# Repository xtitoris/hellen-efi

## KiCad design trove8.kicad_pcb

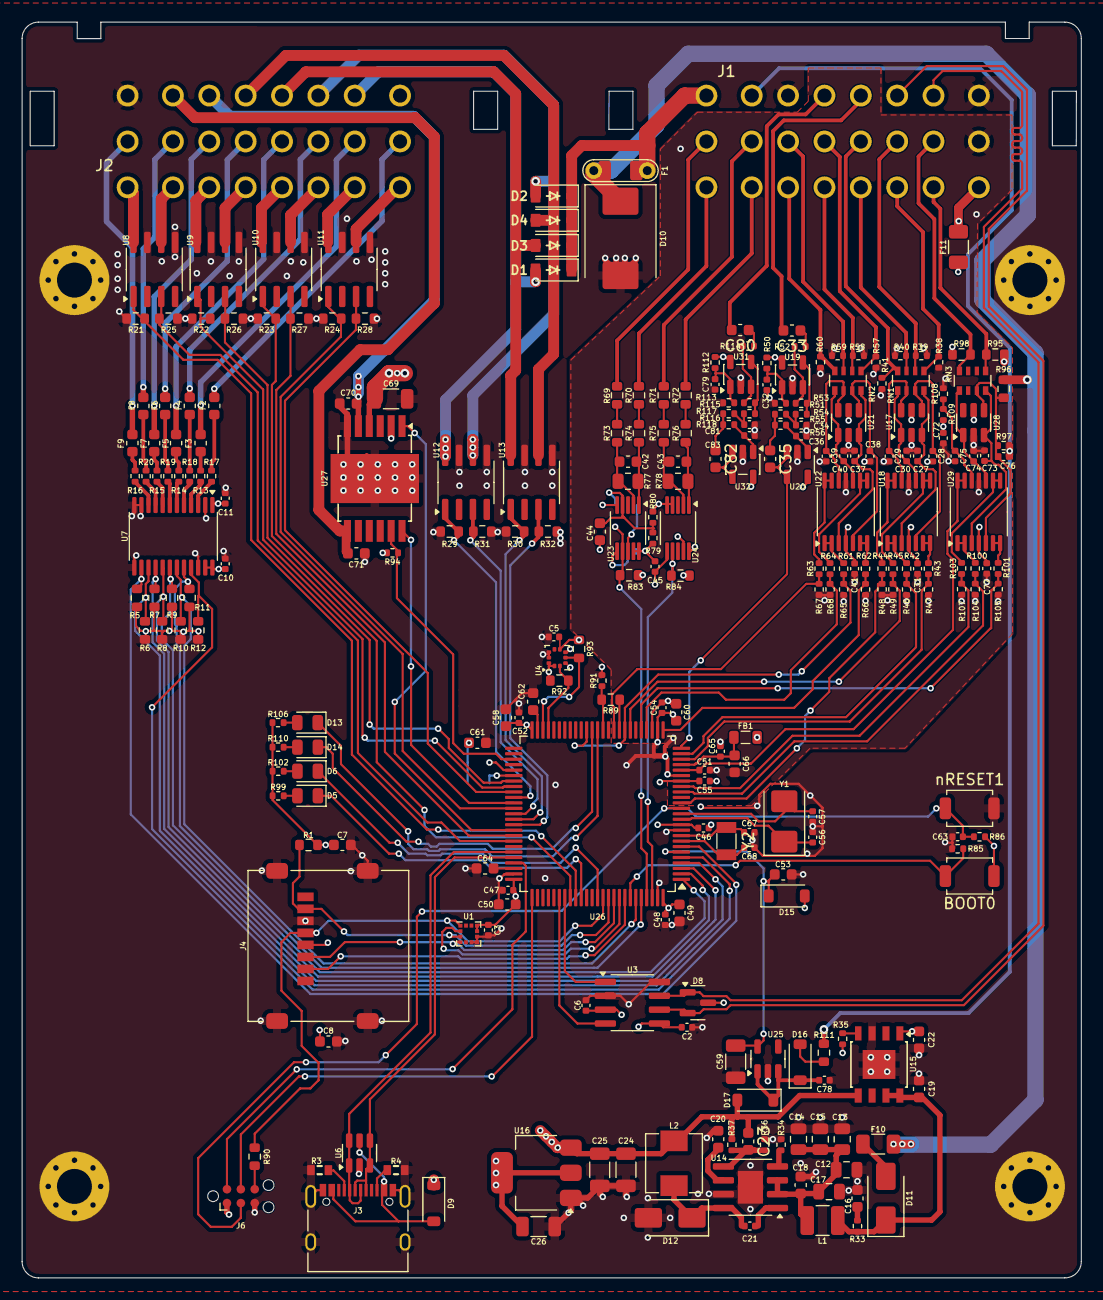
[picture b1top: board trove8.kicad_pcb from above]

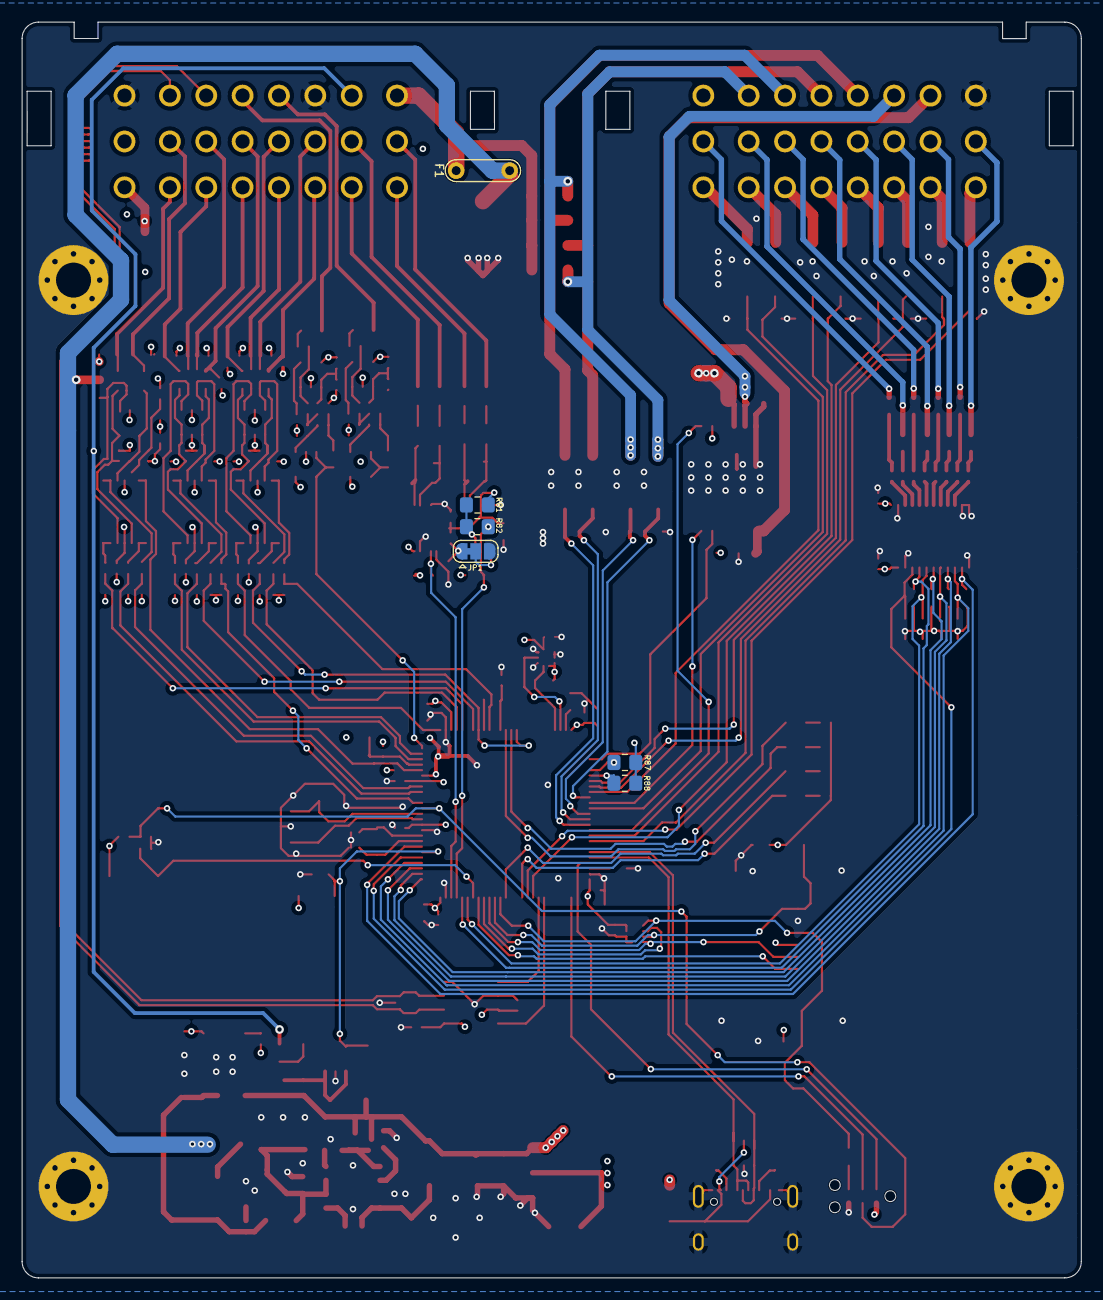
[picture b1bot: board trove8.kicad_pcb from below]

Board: 4 copper layers, 97.0 x 115.0 mm, 274 parts (5 on the bottom side), 204 nets.

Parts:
BOOT0: SW_Push; SW_SPST_TS-1088-xR020
C2, C3, C5, C6, C10, C11, C21, C27, C28, C29, C30, C31, C37, C38, C39, C40, C41, C45, C46, C47, C48, C51, C52, C54, C55, C63, C65, C72, C73, C74, C75, C77, C78: 100n; C_0402_1005Metric
C7, C8: 22u; C_0603_1608Metric
C12, C13, C14, C15, C17: 10u; C_0805_2012Metric
C16, C49, C50, C53, C58, C60, C66: 4.7u; C_0603_1608Metric
C18, C19, C22, C44, C61: 1u; C_0603_1608Metric
C20, C70, C71: 10n; C_0603_1608Metric
C23, C35, C82: 330p; C_0603_1608Metric
C24, C69: 10u; C_1206_3216Metric
C25, C26, C59: 47u; C_1206_3216Metric
C32, C79: 10n; C_0402_1005Metric
C33, C80: 3.3n; C_0603_1608Metric
C34, C81: 680p; C_0402_1005Metric
C36, C83: 47p; C_0402_1005Metric
C42, C43: 1n; C_0603_1608Metric
C56, C57: 18p; C_0402_1005Metric
C62, C64: 2.2u; C_0603_1608Metric
C67, C68: 15p; C_0402_1005Metric
C76: 1u; C_0402_1005Metric
D1, D2, D3, D4: B5819W; SOD-123
D5: RED; LED_0805_2012Metric
D6: GREEN; LED_0805_2012Metric
D8: PESD1CAN; SOT-23
D9, D15, D16, D17: 1N5819WS; D_SOD-123
D10: SM15T33CA; D_SMC
D11, D12: SS34; D_SMA
D13: BLUE; LED_0805_2012Metric
D14: YELLOW; LED_0805_2012Metric
F1: 12H1500D; PAD-1206-PAD
F2, F3, F4, F5, F6, F7, F8, F9: 50mA; Fuse_0603_1608Metric
F10: Polyfuse; Fuse_1206_3216Metric
F11: 120mA; Fuse_1206_3216Metric
FB1: Ferrite_Bead; L_0805_2012Metric
H1, H2, H3, H4: M3; MountingHole_3.2mm_M3_Pad_Via
J1: CONN_INPUTS; Delphi_Sicma_24_Black
J2: CONN_OUTPUTS; Delphi_Sicma_24_Grey
J3: USB_C
J4: Micro_SD_Card; microSD_HC_Molex_47219-2001
J6: Conn_01x06; Tag-Connect_TC2030-IDC-NL_2x03_P1.27mm_Vertical
JP1: Jumper_3_Bridged12; SolderJumper-3_P1.3mm_Bridged12_RoundedPad1.0x1.5mm
L1: 2.2u; L_1210_3225Metric
L2: 10u; MWSA0503
NT1: NetTie_2; NetTie-2_SMD_Pad0.5mm
R1: 33k; R_0603_1608Metric
R3, R4: 5.6k; R0603
R5, R6, R7, R8, R9, R10, R11, R12, R21, R22, R23, R24, R25, R26, R27, R28, R29, R30, R31, R32, R69, R70, R71, R72, R73, R74, R75, R76, R83, R84: 4.7k; R_0603_1608Metric
R13, R14, R15, R16, R17, R18, R19, R20: 10; R_0402_1005Metric
R33: 1; R_0402_1005Metric
R34, R35, R85, R86, R91, R94, R97: 10k; R_0402_1005Metric
R36, R54, R116: 12k; R_0402_1005Metric
R37: 68k; R_0402_1005Metric
R38, R39, R40, R41, R53, R57, R58, R59, R60, R115: 470k; R_0402_1005Metric
R42, R43, R44, R45, R46, R47, R48, R49, R61, R62, R63, R64, R65, R66, R67, R68, R100, R101, R103, R104, R105, R107, R108, R109: 4k7; R_0402_1005Metric
R50, R51, R56, R112, R113, R118: 33k; R_0402_1005Metric
R52, R55, R114, R117: 100k; R_0402_1005Metric
R77, R78: DNP; R_0805_2012Metric
R79, R80: 1k; R_0402_1005Metric
R81, R82, R87, R88: DNP; R_0805_2012Metric_Pad1.20x1.40mm_HandSolder
R89: 0; R_0603_1608Metric
R90: 100; R_0603_1608Metric
R92, R93: 2k2; R_0603_1608Metric
R95, R98: 2.7k; R_0603_1608Metric
R96: 48.7k; R_0603_1608Metric
R99, R102, R106, R110: 470; R_0402_1005Metric
R111: 6.8k; R_0603_1608Metric
RN1, RN2, RN3: 10k; R_Array_Convex_4x0603
U1: LIS2DW12TR; LGA-12_2x2mm_P0.5mm
U3: TJA1051T-3; SOIC-8_3.9x4.9mm_P1.27mm
U4: LPS22HB; ST_HLGA-10_2x2mm_P0.5mm_LayoutBorder3x2y
U6: USBLC6-2SC6; SOT-23-6
U7: SN74LVC4245APWR; TSSOP-24_4.4x7.8mm_P0.65mm
U8, U9, U10, U11, U12, U13: VNLD5160TR-E; SOIC-8_3.9x4.9mm_P1.27mm
U14: LMR14020; SOIC-8-1EP_3.9x4.9mm_P1.27mm_EP2.29x3mm
U15: TLS115; Infineon_PG-DSO-8-43
U16: AMS1117-3.3; SOT-223-3_TabPin2
U17, U21, U28: SRV05-4; SOT-23-6
U18, U22, U29: MCP6004; TSSOP-14_4.4x5mm_P0.65mm
U19, U20, U31, U32: LMV321; SOT-23-5
U23, U24: MAX9924; MSOP-10_3x3mm_P0.5mm
U25: MIC5205-3.3YM5; SOT-23-5
U26: STM32F427VGTx; LQFP-100_14x14mm_P0.5mm
U27: TLE9201SG; Infineon_PG-DSO-12-9
Y1: 20MHz; Crystal_SMD_5032-2Pin_5.0x3.2mm
Y2: 32.768 kHz; Crystal_SMD_3215-2Pin_3.2x1.5mm
nRESET1: SW_Push; SW_SPST_TS-1088-xR020

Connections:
+3.3V: BOOT0.2, C2.1, C3.1, C5.1, C7.1, C8.1, C10.1, C26.1, C46.2, C47.2, C48.2, C49.2, C50.2, C52.2, C54.2, C55.2, C58.2, C60.2, D15.2 (A), FB1.1, J4.4 (VDD), J6.1, R1.1, R35.2, R50.2, R83.1, R84.1, R86.2, R92.2, R93.2, R94.2, R99.1, R102.1, R106.1, R110.1, R112.2, U1.9 (Vdd), U1.10 (Vdd_IO), U3.5 (VIO), U4.1 (Vdd_IO), U4.6 (~CS), U4.10 (VDD), U7.23 (V_{CCB}), U7.24 (V_{CCB}), U16.2 (VO), U19.5 (V+), U20.5 (V+), U26.11 (VDD), U26.19 (VDD), U26.28 (VDD), U26.50 (VDD), U26.75 (VDD), U26.100 (VDD), U27.2 (VSO), U31.5 (V+), U32.5 (V+)
+5V: C6.1, C11.1, C23.1, C24.1, C25.1, C45.1, D9.1 (K), D17.2 (A), JP1.1 (A), L2.2, R37.2, R79.1, U3.3 (VCC), U7.1 (V_{CCA}), U15.5 (ADJ), U16.3 (VI), U23.9 (INT_THRS), U23.10 (VCC), U24.10 (VCC)
+5VA: C22.1, C31.1, C41.1, C72.2, C77.1, F11.1, R95.1, R98.1, R109.1, U15.1 (OUT), U17.5 (VP), U18.4 (V+), U21.5 (VP), U22.4 (V+), U28.5 (VP), U29.4 (V+)
+12V_IN: C69.2, D1.1 (K), D2.1 (K), D3.1 (K), D4.1 (K), F1.1, J1.C1, U27.4 (VS)
+12V_PERM: J1.C2, R111.1
+12V_PROT: C19.1, D11.1 (K), L1.1, R33.1, U15.7 (EN), U15.8 (IN)
+12V_RAW: D10.1 (A1), F1.2, F10.1, R96.1
/ACC_CS: U1.2 (~CS), U26.92 (PB6)
/Analog 3 Pullup/IN1_PRE: C73.1, RN3.8 (R1.2), U28.3 (IO2), U29.3 (+)
/Analog 3 Pullup/IN2_PRE: C74.1, RN3.5 (R4.2), U28.1 (IO1), U29.10 (+)
/Analog 3 Pullup/VIGN_PRE: C76.1, R96.2, R97.1, RN3.7 (R2.2), U28.4 (IO3), U29.5 (+)
/Analog 3 Pullup/VREF_PRE: C75.1, R108.1, R109.2, U29.12 (+)
/BARO_SCL: R92.1, U4.2 (SCL), U26.47 (PB10)
/BARO_SDA: R93.1, U4.4 (SDA), U26.48 (PB11)
/CAN1_RX: U3.4 (RXD), U26.81 (PD0)
/CAN1_TX: U3.1 (TXD), U26.82 (PD1)
/CAN_N: D8.2 (D), J1.C6, U3.6 (CANL)
/CAN_P: D8.1 (G), J1.C7, U3.7 (CANH)
/DC1_DIS: R94.1, U26.53 (PB14), U27.11 (DIS)
/IGN_1: F9.1, J2.B1
/IGN_2: F8.1, J2.B2
/IGN_3: F7.1, J2.B3
/IGN_4: F6.1, J2.B4
/IGN_5: F5.1, J2.B5
/IGN_6: F4.1, J2.B6
/IGN_7: F3.1, J2.B7
/IGN_8: F2.1, J2.B8
/INJ_1: J2.A1, U8.8 (D1)
/INJ_2: J2.A2, U8.6 (D2)
/INJ_3: J2.A3, U9.8 (D1)
/INJ_4: J2.A4, U9.6 (D2)
/INJ_5: J2.A5, U10.8 (D1)
/INJ_6: J2.A6, U10.6 (D2)
/INJ_7: J2.A7, U11.8 (D1)
/INJ_8: J2.A8, U11.6 (D2)
/IN_AC_CLUTCH: J1.B5, R41.1, RN1.4 (R4.1)
/IN_CAM_NEGATIVE: J1.A2, R72.2
/IN_CAM_PRIMARY: J1.B2, R71.2
/IN_CLT: J1.A7, R95.2, RN3.1 (R1.1)
/IN_CRANK_NEGATIVE: J1.A1, R70.2
/IN_CRANK_PRIMARY: J1.B1, R69.2
/IN_IAT: J1.B7, R98.2, RN3.4 (R4.1)
/IN_KNOCK: C33.2, J1.C5
/IN_KNOCK2: C80.2, J1.C4
/IN_MAP: J1.A5, R40.1, RN1.3 (R3.1)
/IN_O2S: J1.A6, R38.1, RN1.1 (R1.1)
/IN_O2S2: J1.B6, R39.1, RN1.2 (R2.1)
/IN_PPS1: J1.A4, R58.1, RN2.2 (R2.1)
/IN_PPS2: J1.B4, R57.1, RN2.1 (R1.1)
/IN_TPS_1: J1.A3, R60.1, RN2.4 (R4.1)
/IN_TPS_2: J1.B3, R59.1, RN2.3 (R3.1)
/Knock1/FILTERED_1: C82.2, U32.3 (-), U32.4
/Knock1/V_mid: C79.2, R112.1, R113.1, U31.1 (+)
/Knock/V_mid: C32.2, R50.1, R51.1, U19.1 (+)
/MCU/BOOT0: BOOT0.1, R85.1, U26.94 (BOOT0)
/MCU/BOOT1: R89.2, R91.1, U26.37 (PB2)
/MCU/LED1: D5.1 (K), U26.85 (PD4)
/MCU/LED2: D6.1 (K), U26.88 (PD7)
/MCU/LED3: D13.1 (K), U26.38 (PE7)
/MCU/LED4: D14.1 (K), U26.39 (PE8)
/MCU/SWCLK: J6.4, U26.76 (PA14)
/MCU/SWDIO: J6.2, U26.72 (PA13)
/MCU/SWO: J6.6, R90.2
/MCU/VDDA: C65.1, C66.1, FB1.2, U26.22 (VDDA)
/MCU/nRESET: C63.2, J6.3, R86.1, U26.14 (NRST), nRESET1.1
/MCU_IGN1: R5.2, U7.14 (B8), U26.7 (PC13)
/MCU_IGN2: R6.2, U7.15 (B7), U26.4 (PE5)
/MCU_IGN3: R7.2, U7.16 (B6), U26.3 (PE4)
/MCU_IGN4: R8.2, U7.17 (B5), U26.2 (PE3)
/MCU_IGN5: R9.2, U7.18 (B4), U26.1 (PE2)
/MCU_IGN6: R10.2, U7.19 (B3), U26.95 (PB8)
/MCU_IGN7: R11.2, U7.20 (B2), U26.96 (PB9)
/MCU_IGN8: R12.2, U7.21 (B1), U26.5 (PE6)
/MCU_INJ1: R21.2, U8.1 (IN1), U26.84 (PD3)
/MCU_INJ2: R25.2, U8.3 (IN2), U26.68 (PA9)
/MCU_INJ3: R22.2, U9.1 (IN1), U26.58 (PD11)
/MCU_INJ4: R26.2, U9.3 (IN2), U26.57 (PD10)
/MCU_INJ5: R23.2, U10.1 (IN1), U26.83 (PD2)
/MCU_INJ6: R27.2, U10.3 (IN2), U26.67 (PA8)
/MCU_INJ7: R24.2, U11.1 (IN1), U26.62 (PD15)
/MCU_INJ8: R28.2, U11.3 (IN2), U26.59 (PD12)
/MCU_IN_AC_CLUTCH: R45.1, R49.2, U26.32 (PA7)
/MCU_IN_AUX_PU1: R89.1, U26.34 (PC5)
/MCU_IN_CAM: R84.2, U24.7 (COUT), U26.98 (PE1)
/MCU_IN_CLT: R100.1, R104.2, U26.17 (PC2)
/MCU_IN_CRANK: R82.1, R83.2, U23.7 (COUT), U26.97 (PE0)
/MCU_IN_IAT: R103.1, R107.2, U26.18 (PC3)
/MCU_IN_KNOCK: C35.2, U20.3 (-), U20.4, U26.25 (PA2)
/MCU_IN_MAP: R44.1, R48.2, U26.15 (PC0)
/MCU_IN_O2S: R42.1, R46.2, U26.24 (PA1)
/MCU_IN_O2S2: R43.1, R47.2, U26.23 (PA0)
/MCU_IN_PPS1: R62.1, R66.2, U26.26 (PA3)
/MCU_IN_PPS2: R61.1, R65.2, U26.33 (PC4), U26.40 (PE9)
/MCU_IN_TPS_1: R64.1, R68.2, U26.29 (PA4)
/MCU_IN_TPS_2: R63.1, R67.2, U26.35 (PB0)
/MCU_IN_VIGN: R101.1, R105.2, U26.30 (PA5)
/MCU_PWM1: R29.2, U12.1 (IN1), U26.60 (PD13)
/MCU_PWM2: R31.2, U12.3 (IN2), U26.63 (PC6)
/MCU_PWM3: R30.2, U13.1 (IN1), U26.64 (PC7)
/MCU_PWM4: R32.2, U13.3 (IN2), U26.65 (PC8)
/MCU_PWM5: U26.66 (PC9), U27.1 (DIR)
/MCU_PWM6: U26.61 (PD14), U27.12 (PWM)
/MCU_VREF: C51.1, U26.21 (VREF+), U29.13 (-), U29.14
/OUT_DH: C70.2, J2.C3, U27.5 (OUT1)
/OUT_DL: C71.1, J2.C2, U27.7 (OUT2)
/OUT_LS1: D1.2 (A), J2.C7, U12.8 (D1)
/OUT_LS2: D2.2 (A), J2.C6, U12.6 (D2)
/OUT_LS3: D3.2 (A), J2.C5, U13.8 (D1)
/OUT_LS4: D4.2 (A), J2.C4, U13.6 (D2)
/SD_CS: J4.2 (DAT3/CD), U26.93 (PB7)
/SPI1_MISO: J4.7 (DAT0), R1.2, U1.3 (SA0/SDO), U26.90 (PB4)
/SPI1_MOSI: J4.3 (CMD), U1.4 (SDA/SDI), U26.91 (PB5)
/SPI1_SCK: J4.5 (CLK), R90.1, U1.1 (SCL/SPC), U26.89 (PB3)
/USB_D+: J3.A6 (D+), J3.B6 (D+), U6.3 (I/O2), U6.4 (I/O2), U26.71 (PA12)
/USB_D-: J3.A7 (D-), J3.B7 (D-), U6.1 (I/O1), U6.6 (I/O1), U26.70 (PA11)
/USB_VBUS: D9.2 (A), J3.A4 (VBUS), J3.A9 (VBUS), J3.B4 (VBUS), J3.B9 (VBUS), U6.5 (VBUS)
/VBAT: C53.1, C59.1, D15.1 (K), U25.5 (OUT), U26.6 (VBAT)
/VReg/5V_SENSOR_1_PG: R35.1, U15.4 (PG)
/VReg/12V_PRE: C12.1, C13.1, C14.1, C15.1, C17.1, C18.1, L1.2, U14.2 (VIN), U14.3 (EN)
GND: C2.2, C3.2, C5.2, C6.2, C7.2, C8.2, C10.2, C11.2, C12.2, C13.2, C14.2, C15.2, C16.2, C17.2, C18.2, C19.2, C20.2, C22.2, C24.2, C25.2, C26.2, C44.2, C45.2, C46.1, C47.1, C48.1, C49.1, C50.1, C52.1, C53.2, C54.1, C55.1, C56.2, C57.2, C58.1, C59.2, C60.1, C61.2, C62.2, C63.1, C64.2, C67.2, C68.2, C69.1, C70.1, C71.2, C78.2, D8.3 (S), D10.2 (A2), D12.2 (A), H1.1 (1_1), H2.1 (1_1), H3.1 (1_1), H4.1 (1_1), J1.C3, J1.C8, J2.C1, J2.C8, J3.A1 (GND), J3.A12 (GND), J3.B1 (GND), J3.B12 (GND), J3.S1 (SHIELD), J4.6 (VSS), J4.9 (SHIELD), J6.5, JP1.3 (B), NT1.1, R3.1, R4.1, R5.1, R6.1, R7.1, R8.1, R9.1, R10.1, R11.1, R12.1, R21.1, R22.1, R23.1, R24.1, R25.1, R26.1, R27.1, R28.1, R29.1, R30.1, R31.1, R32.1, R34.2, R36.2, R80.1, R85.2, R91.2, U1.6 (GND), U1.7 (RES), U1.8 (GND), U3.2 (GND), U3.8 (S), U4.3 (GND), U4.5 (SA0), U4.8 (GND), U4.9 (GND), U6.2 (GND), U7.2 (DIR), U7.11 (GND), U7.12 (GND), U7.13 (GND), U7.22 (~OE), U8.5 (S2), U8.7 (S1), U9.5 (S2), U9.7 (S1), U10.5 (S2), U10.7 (S1), U11.5 (S2), U11.7 (S1), U12.5 (S2), U12.7 (S1), U13.5 (S2), U13.7 (S1), U14.7 (GND), U14.9 (GND), U15.3 (GND), U15.9 (GND), U16.1 (GND), U23.5 (GND), U24.4 (BIAS), U24.5 (GND), U24.6 (ZERO_EN), U24.9 (INT_THRS), U25.2 (GND), U26.10 (VSS), U26.27 (VSS), U26.74 (VSS), U26.99 (VSS), U27.6 (GND), U27.13 (GND), nRESET1.2
GNDA: C27.2, C28.2, C29.2, C30.2, C31.2, C32.1, C34.1, C36.1, C37.2, C38.2, C39.2, C40.2, C41.2, C51.2, C65.2, C66.2, C72.1, C73.2, C74.2, C75.2, C76.2, C77.2, C79.1, C81.1, C83.1, J1.B8, NT1.2, R38.2, R39.2, R40.2, R41.2, R46.1, R47.1, R48.1, R49.1, R51.2, R57.2, R58.2, R59.2, R60.2, R65.1, R66.1, R67.1, R68.1, R97.2, R104.1, R105.1, R107.1, R108.2, R113.2, U17.2 (VN), U18.11 (V-), U19.2 (V-), U20.2 (V-), U21.2 (VN), U22.11 (V-), U26.20 (VSSA), U28.2 (VN), U29.11 (V-), U31.2 (V-), U32.2 (V-)
unnamed: C16.1, R33.2
unnamed: C33.1, R52.2
unnamed: C34.2, R54.1, R55.2
unnamed: C35.1, R55.1, R56.2
unnamed: C61.1, R87.1, R88.1
unnamed: C80.1, R114.2
unnamed: C81.2, R116.1, R117.2
unnamed: C82.1, R117.1, R118.2
unnamed: D5.2 (A), R99.2
unnamed: D6.2 (A), R102.2
unnamed: D11.2 (A), F10.2
unnamed: C21.2, D12.1 (K), L2.1, U14.8 (SW)
unnamed: D13.2 (A), R106.2
unnamed: D14.2 (A), R110.2
unnamed: D16.2 (A), R111.2
unnamed: C78.1, D16.1 (K), D17.1 (K), U25.1 (IN), U25.3 (EN)
unnamed: F2.2, R17.2
unnamed: F3.2, R13.2
unnamed: F4.2, R18.2
unnamed: F5.2, R14.2
unnamed: F6.2, R19.2
unnamed: F7.2, R15.2
unnamed: F8.2, R20.2
unnamed: F9.2, R16.2
unnamed: F11.2, J1.A8
unnamed: J3.A5 (CC1), R3.2
unnamed: J3.B5 (CC2), R4.2
unnamed: JP1.2 (C), U23.6 (ZERO_EN)
unnamed: R53.1, R54.2, U19.4
unnamed: R69.1, R73.2
unnamed: R70.1, R74.2
unnamed: R71.1, R75.2
unnamed: R72.1, R76.2
unnamed: R115.1, R116.2, U31.4
unnamed: C27.1, RN1.8 (R1.2), U17.3 (IO2), U18.3 (+)
unnamed: C28.1, RN1.7 (R2.2), U17.4 (IO3), U18.5 (+)
unnamed: C29.1, RN1.6 (R3.2), U17.6 (IO4), U18.12 (+)
unnamed: C30.1, RN1.5 (R4.2), U17.1 (IO1), U18.10 (+)
unnamed: C37.1, RN2.8 (R1.2), U21.3 (IO2), U22.3 (+)
unnamed: C38.1, RN2.7 (R2.2), U21.4 (IO3), U22.5 (+)
unnamed: C39.1, RN2.6 (R3.2), U21.6 (IO4), U22.12 (+)
unnamed: C40.1, RN2.5 (R4.2), U21.1 (IO1), U22.10 (+)
unnamed: R17.1, U7.3 (A1)
unnamed: R13.1, U7.4 (A2)
unnamed: R18.1, U7.5 (A3)
unnamed: R14.1, U7.6 (A4)
unnamed: R19.1, U7.7 (A5)
unnamed: R15.1, U7.8 (A6)
unnamed: R20.1, U7.9 (A7)
unnamed: R16.1, U7.10 (A8)
unnamed: C21.1, U14.1 (BOOT)
unnamed: C23.2, R36.1, R37.1, U14.5 (FB)
unnamed: R34.1, U14.4 (RT)
unnamed: C20.1, U14.6 (SS)
unnamed: R42.2, U18.1, U18.2 (-)
unnamed: R43.2, U18.6 (-), U18.7
unnamed: R45.2, U18.8, U18.9 (-)
unnamed: R44.2, U18.13 (-), U18.14
unnamed: R52.1, R53.2, U19.3 (-)
unnamed: C36.2, R56.1, U20.1 (+)
unnamed: R61.2, U22.1, U22.2 (-)
unnamed: R62.2, U22.6 (-), U22.7
unnamed: R64.2, U22.8, U22.9 (-)
unnamed: R63.2, U22.13 (-), U22.14
unnamed: C44.1, R79.2, R80.2, R81.2, U23.4 (BIAS)
unnamed: R81.1, R82.2, U23.8 (EXT)
unnamed: C42.2, R74.1, R77.1, U23.1 (IN+)
unnamed: C42.1, R73.1, R77.2, U23.2 (IN-)
unnamed: C43.2, R76.1, R78.1, U24.1 (IN+)
unnamed: C43.1, R75.1, R78.2, U24.2 (IN-)
unnamed: C68.1, U26.8 (PC14), Y2.1
unnamed: C67.1, U26.9 (PC15), Y2.2
unnamed: R87.2, U26.55 (PD8)
unnamed: R88.2, U26.56 (PD9)
unnamed: C56.1, U26.12 (PH0), Y1.1
unnamed: C57.1, U26.13 (PH1), Y1.2
unnamed: C62.1, U26.49 (VCAP_1)
unnamed: C64.1, U26.73 (VCAP_2)
unnamed: R100.2, U29.1, U29.2 (-)
unnamed: R101.2, U29.6 (-), U29.7
unnamed: R103.2, U29.8, U29.9 (-)
unnamed: R114.1, R115.2, U31.3 (-)
unnamed: C83.2, R118.1, U32.1 (+)

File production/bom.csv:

Designator,Footprint,Quantity,Value,LCSC Part #
"BOOT0, NRESET1",SW_SPST_TS-1088-xR020,2,SW_Push,C720477
"C10, C11, C2, C21, C27, C28, C29, C3, C30, C31, C37, C38, C39, C40, C41, C45, C46, C47, C48, C5, C51, C52, C54, C55, C6, C63, C65, C72, C73, C74, C75, C77, C78",0402,33,100n,C1525
"C12, C13, C14, C15, C17",0805,5,10u,C440198
"C16, C49, C50, C53, C58, C60, C66",0603,7,4.7u,C19666
"C18, C19, C22, C44, C61",0603,5,1u,C15849
"C20, C70, C71",0603,3,10n,C57112
"C23, C35, C82",0603,3,330p,C1664
"C24, C69",1206,2,10u,C13585
"C25, C26, C59",1206,3,47u,C96123
"C32, C79",0402,2,10n,C15195
"C33, C80",0603,2,3.3n,C1613
"C34, C81",0402,2,680p,C307451
"C36, C83",0402,2,47p,C1567
"C42, C43",0603,2,1n,C1588
"C56, C57",0402,2,18p,C1549
"C62, C64",0603,2,2.2u,C23630
"C67, C68",0402,2,15p,C1548
"C7, C8",0603,2,22u,C59461
C76,0402,1,1u,C52923
"D1, D2, D3, D4",SOD-123,4,B5819W,C8598
D10,D_SMC,1,SM15T33CA,C151281
"D11, D12",D_SMA,2,SS34,C8678
D13,0805,1,BLUE,C34499
D14,0805,1,YELLOW,C2296
"D15, D16, D17, D9",D_SOD-123,4,1N5819WS,C191023
D5,0805,1,RED,C84256
D6,0805,1,GREEN,C2297
D8,SOT-23,1,PESD1CAN,C343993
F1,PAD-1206-PAD,1,12H1500D,C182446
F10,1206,1,Polyfuse,C492011
F11,1206,1,120mA,C20982
"F2, F3, F4, F5, F6, F7, F8, F9",0603,8,50mA,C369141
FB1,0805,1,Ferrite_Bead,C1015
J3,USB_C,1,USB_C,C2927038
J4,microSD_HC_Molex_47219-2001,1,Micro_SD_Card,C164170
L1,1210,1,2.2u,C75646
L2,MWSA0503,1,10u,C408412
R1,0603,1,33k,C4216
"R10, R11, R12, R21, R22, R23, R24, R25, R26, R27, R28, R29, R30, R31, R32, R5, R6, R69, R7, R70, R71, R72, R73, R74, R75, R76, R8, R83, R84, R9",0603,30,4.7k,C23162
"R100, R101, R103, R104, R105, R107, R108, R109, R42, R43, R44, R45, R46, R47, R48, R49, R61, R62, R63, R64, R65, R66, R67, R68",0402,24,4k7,C281778
"R102, R106, R110, R99",0402,4,470,C25117
R111,0603,1,6.8k,C23212
"R112, R113, R118, R50, R51, R56",0402,6,33k,C25779
"R114, R117, R52, R55",0402,4,100k,C25741
"R115, R38, R39, R40, R41, R53, R57, R58, R59, R60",0402,10,470k,C25790
"R116, R36, R54",0402,3,12k,C25752
"R13, R14, R15, R16, R17, R18, R19, R20",0402,8,10,C25077
"R3, R4",R0603,2,5.6k,C23189
R33,0402,1,1,C25086
"R34, R35, R85, R86, R91, R94, R97",0402,7,10k,C25744
R37,0402,1,68k,C36871
"R79, R80",0402,2,1k,C11702
R89,0603,1,0,C21189
R90,0603,1,100,C22775
"R92, R93",0603,2,2k2,C4190
"R95, R98",0603,2,2.7k,C13167
R96,0603,1,48.7k,C23063
"RN1, RN2, RN3",R_Array_Convex_4x0603,3,10k,C29718
U1,LGA-12_2x2mm_P0.5mm,1,LIS2DW12TR,C50385411
"U10, U11, U12, U13, U8, U9",SOIC-8_3.9x4.9mm_P1.27mm,6,VNLD5160TR-E,C377942
U14,SOIC-8-1EP_3.9x4.9mm_P1.27mm_EP2.29x3mm,1,LMR14020,C187824
U15,Infineon_PG-DSO-8-43,1,TLS115,C3747428
U16,SOT-223-3_TabPin2,1,AMS1117-3.3,C6186
"U17, U21, U28",SOT-23-6,3,SRV05-4,C85364
"U18, U22, U29",TSSOP-14_4.4x5mm_P0.65mm,3,MCP6004,C50282
"U19, U20, U31, U32",SOT-23-5,4,LMV321,C7972
"U23, U24",MSOP-10_3x3mm_P0.5mm,2,MAX9924,C5145181
U25,SOT-23-5,1,MIC5205-3.3YM5,
U26,LQFP-100_14x14mm_P0.5mm,1,STM32F427VGTx,C117815
U27,Infineon_PG-DSO-12-9,1,TLE9201SG,C112633
U3,SOIC-8_3.9x4.9mm_P1.27mm,1,TJA1051T-3,C51954344
U4,ST_HLGA-10_2x2mm_P0.5mm_LayoutBorder3x2y,1,LPS22HB,C94049
U6,SOT-23-6,1,USBLC6-2SC6,C7519
U7,TSSOP-24_4.4x7.8mm_P0.65mm,1,SN74LVC4245APWR,C7859
Y1,Crystal_SMD_5032-2Pin_5.0x3.2mm,1,20MHz,C112566
Y2,Crystal_SMD_3215-2Pin_3.2x1.5mm,1,32.768 kHz,C32346

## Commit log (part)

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2025-12-07 Rev 0
2025-12-12 Standalone version without hellen-one
